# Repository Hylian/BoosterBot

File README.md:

BoosterBot
==========

A BoosterPack that turns your TI Launchpad into a fully functional robot!

The BoosterBot attaches underneath any 40-pin Launchpad to give it batteries, wheels, and access to a bunch of sensors; perfect for anyone who wants to get started with MSP430 and robotics, or just wants an easy to use robotics platform to build off of.

Features
--------
* Micro Metal Gearmotors from Pololu
* Powered by 3xAAA batteries
* Five QRE1113 Reflectance sensors for line following and maze solving
* Header for a Sharp IR distance sensor
* Header for a servo
* Compatible with other BoosterPacks, including the FuelTank battery BoosterPack

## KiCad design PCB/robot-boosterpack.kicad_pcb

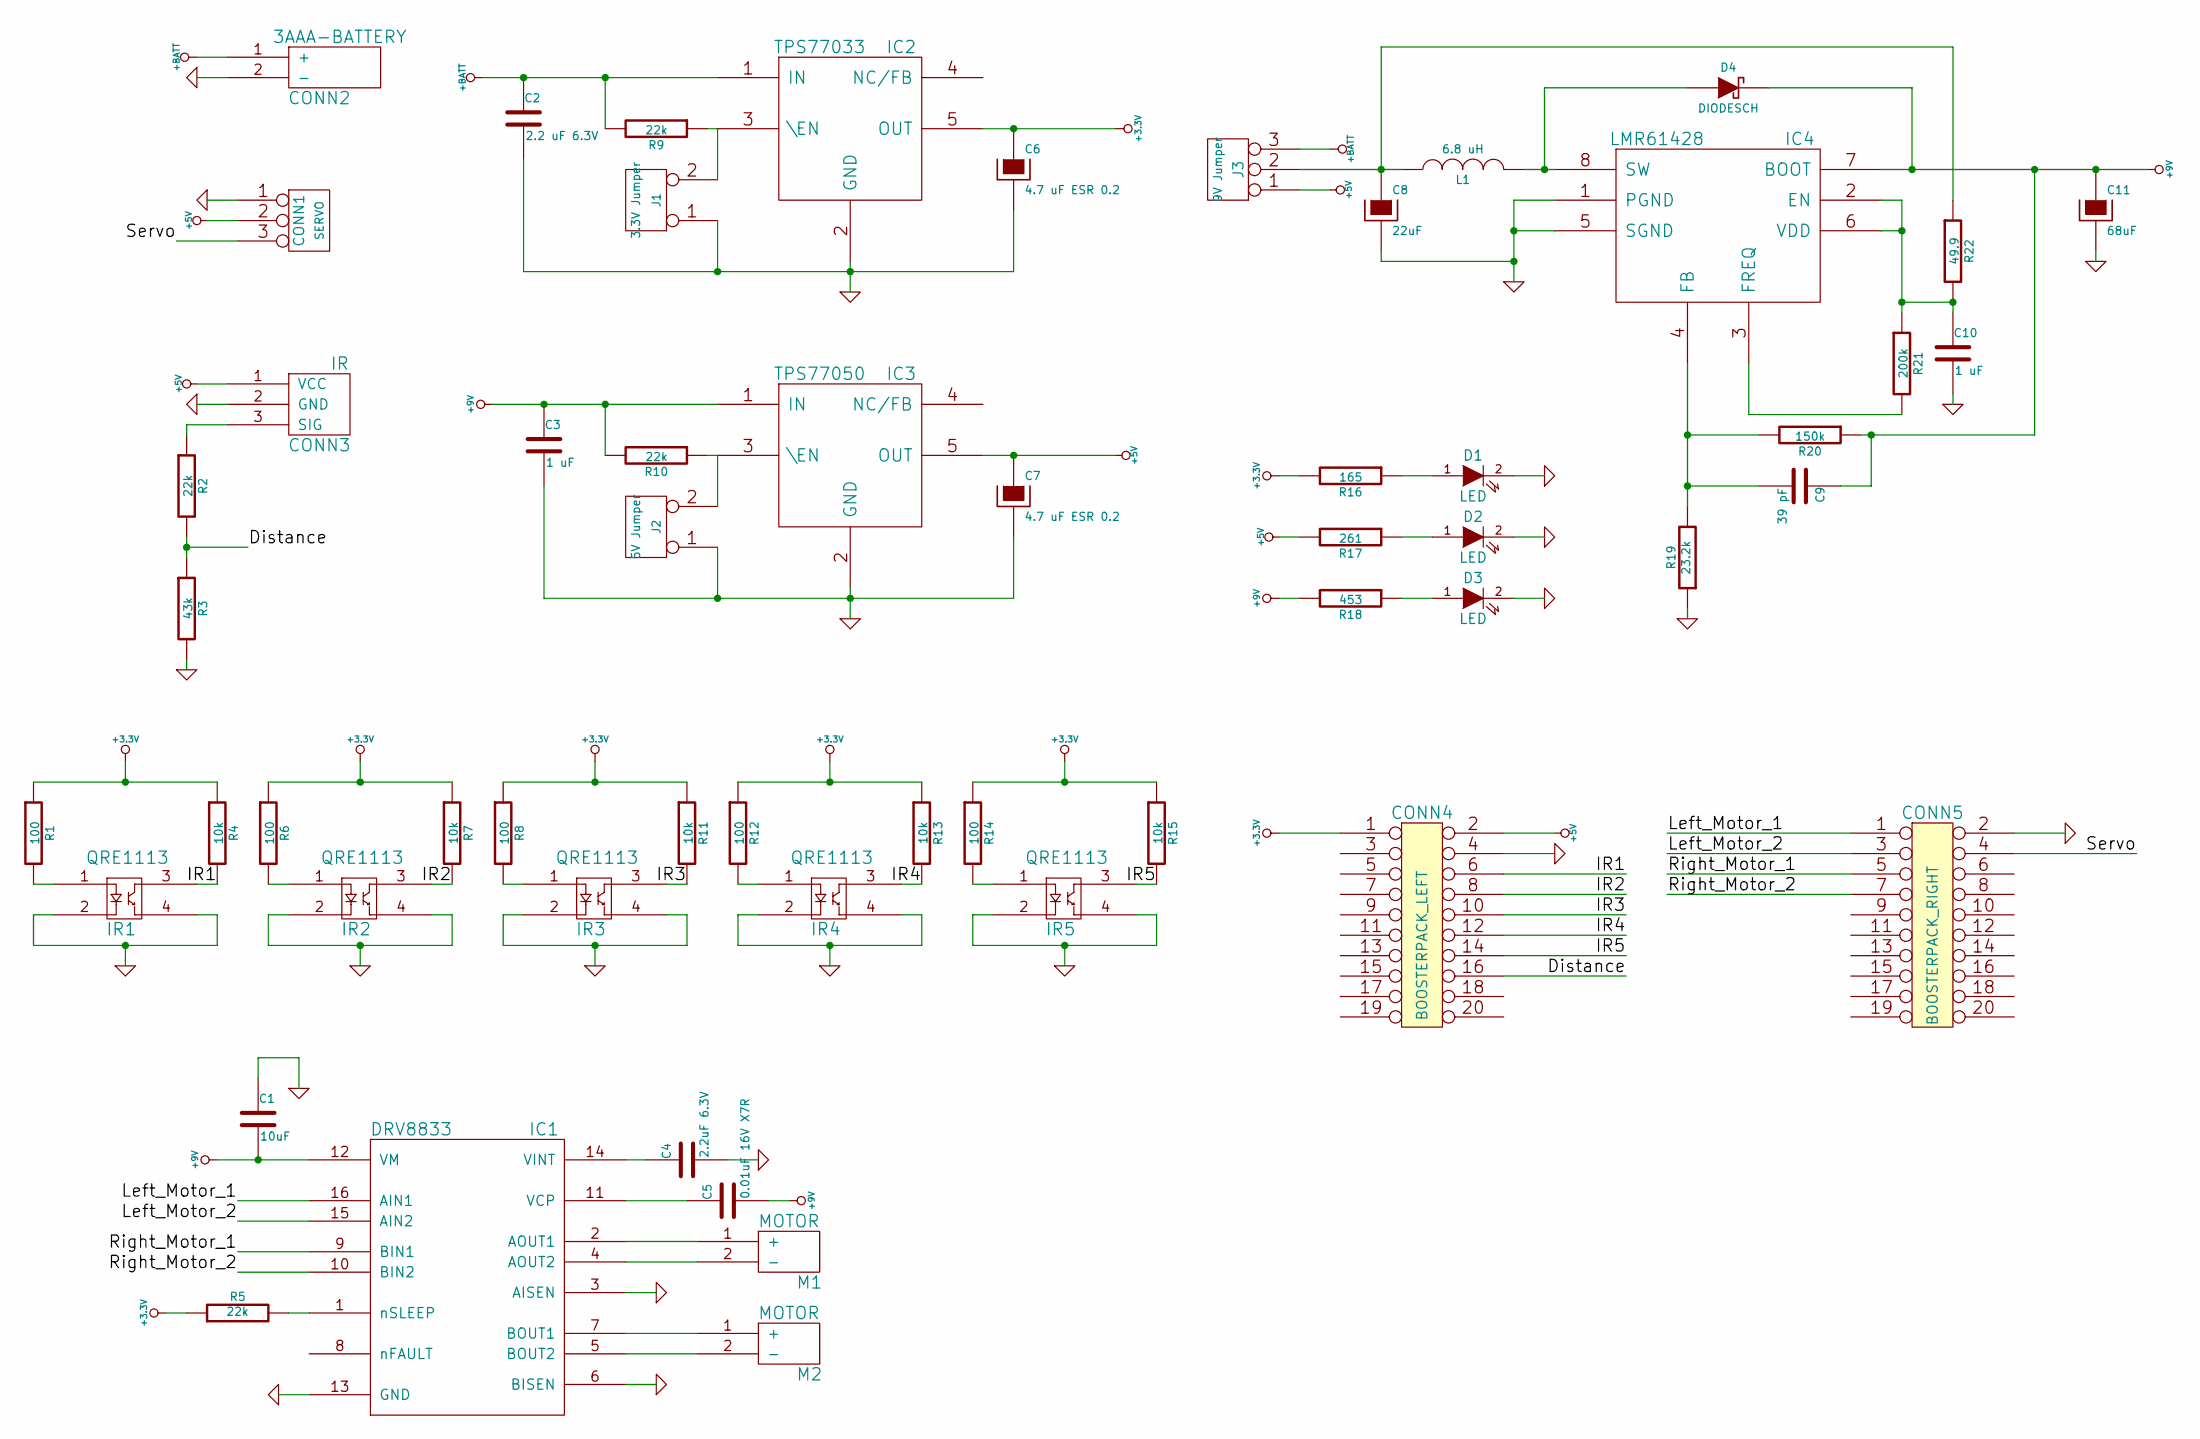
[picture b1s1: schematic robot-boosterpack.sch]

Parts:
C1: 10uF; Digikey # 311-1343-1-ND
C2: 2.2 uF 6.3V; Digikey # 587-1254-1-ND
C3, C10: 1 uF; Digikey # 587-1242-1-ND
C4: 2.2uF 6.3V; Digikey # 587-1254-1-ND
C5: 0.01uF 16V X7R; Digikey # 490-1512-1-ND
C6, C7: 4.7 uF ESR 0.2; Digikey # 478-1772-1-ND
C8: 22uF; Digikey # 399-3716-1-ND
C9: 39 pF
C11: 68uF; Digikey # 399-4698-1-ND
CONN1: SERVO; Digikey # 609-3461-ND
CONN2: 3AAA-BATTERY
CONN3: IR; Digikey # S5751-03-ND
CONN4: BOOSTERPACK_LEFT
CONN5: BOOSTERPACK_RIGHT
D1: LED; Digikey # 160-1448-1-ND
D2: LED; Digikey # 160-1447-1-ND
D3: LED; Digikey # 160-1647-1-ND
D4: DIODESCH; Digikey # MBRS140T3GOSCT-ND
IC1: DRV8833
IC2: TPS77033
IC3: TPS77050
IC4: LMR61428
IR1, IR2, IR3, IR4, IR5: QRE1113
J1: 3.3V Jumper; Digikey # 3M9447-ND
J2: 5V Jumper; Digikey # 3M9447-ND
J3: 9V Jumper; Digikey # 609-3461-ND
L1: 6.8 uH; Digikey # SRN6045-100MCT-ND
M1, M2: MOTOR
R1, R6, R8, R12, R14: 100; Digikey # 311-100HRCT-ND
R2, R5, R9, R10: 22k; Digikey # P22KDBTR-ND
R3: 43k; Digikey # 311-43.0KHRCT-ND
R4, R7, R11, R13, R15: 10k; Digikey # 311-10KGRCT-ND
R16: 165; Digikey # 311-165HRCT-ND
R17: 261; Digikey # P261HCT-ND
R18: 453; Digikey # P453HCT-ND
R19: 23.2k; Digikey # 311-23.2KHRTR-ND
R20: 150k; Digikey # P150KDBCT-ND
R21: 200k; Digikey # P200KDBCT-ND
R22: 49.9; Digikey # P49.9HCT-ND

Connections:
+3.3V: C6.1, CONN4.1, IC2.5 (OUT), R1.1, R4.1, R5.1, R6.1, R7.1, R8.1, R11.1, R12.1, R13.1, R14.1, R15.1, R16.2
+5V: C7.1, CONN1.2 (PM), CONN3.1 (VCC), CONN4.2, IC3.5 (OUT), J3.1, R17.2
+BATT: C2.1, CONN2.1 (+), IC2.1 (IN), J3.3, R9.2
/Distance: CONN4.16, R2.2, R3.1
/IR1: CONN4.6, IR1.3, R4.2
/IR2: CONN4.8, IR2.3, R7.2
/IR3: CONN4.10, IR3.3, R11.2
/IR4: CONN4.12, IR4.3, R13.2
/IR5: CONN4.14, IR5.3, R15.2
/Left_Motor_1: CONN5.1, IC1.16 (AIN1)
/Left_Motor_2: CONN5.3, IC1.15 (AIN2)
/Right_Motor_1: CONN5.5, IC1.9 (BIN1)
/Right_Motor_2: CONN5.7, IC1.10 (BIN2)
/Servo: CONN1.3, CONN5.4
GND: C1.1, C2.2, C3.2, C4.2, C6.2, C7.2, C8.2, C10.2, C11.2, CONN1.1, CONN2.2 (-), CONN3.2 (GND), CONN4.4, CONN5.2, D1.2 (K), D2.2 (K), D3.2 (K), IC1.3 (AISEN), IC1.6 (BISEN), IC1.13 (GND), IC2.2 (GND), IC3.2 (GND), IC4.1 (PGND), IC4.5 (SGND), IR1.2, IR1.4, IR2.2, IR2.4, IR3.2, IR3.4, IR4.2, IR4.4, IR5.2, IR5.4, J1.1, J2.1, R3.2, R19.1
unnamed: C9.2, IC4.4 (FB), R19.2, R20.2
unnamed: IC4.3 (FREQ), R21.2
unnamed: IR4.1, R12.2
unnamed: C10.1, IC4.2 (EN), IC4.6 (VDD), R21.1, R22.2
unnamed: IR3.1, R8.2
unnamed: IR2.1, R6.2
unnamed: C4.1, IC1.14 (VINT)
unnamed: C5.1, IC1.11 (VCP)
unnamed: IC1.1 (nSLEEP), R5.2
unnamed: IR1.1, R1.2
unnamed: CONN3.3 (SIG), R2.1
unnamed: D4.1 (A), IC4.8 (SW), L1.2
unnamed: D3.1 (A), R18.1
unnamed: D2.1 (A), R17.1
unnamed: D1.1 (A), R16.1
unnamed: C8.1, J3.2 (PM), L1.1, R22.1
unnamed: IC3.3 (\EN), J2.2 (PM), R10.1
unnamed: IR5.1, R14.2
unnamed: IC2.3 (\EN), J1.2 (PM), R9.1
unnamed: IC1.7 (BOUT1), M2.1 (+)
unnamed: IC1.5 (BOUT2), M2.2 (-)
unnamed: IC1.4 (AOUT2), M1.2 (-)
unnamed: IC1.2 (AOUT1), M1.1 (+)

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
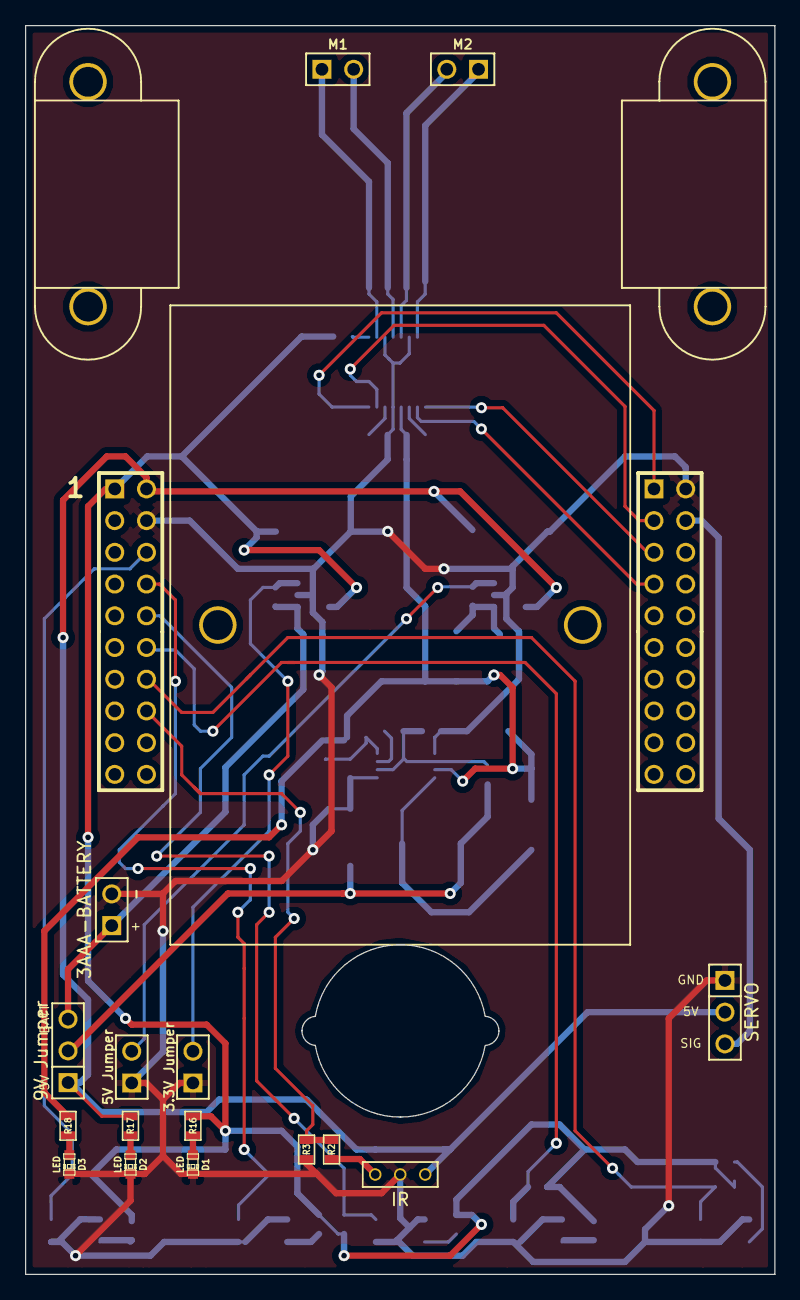
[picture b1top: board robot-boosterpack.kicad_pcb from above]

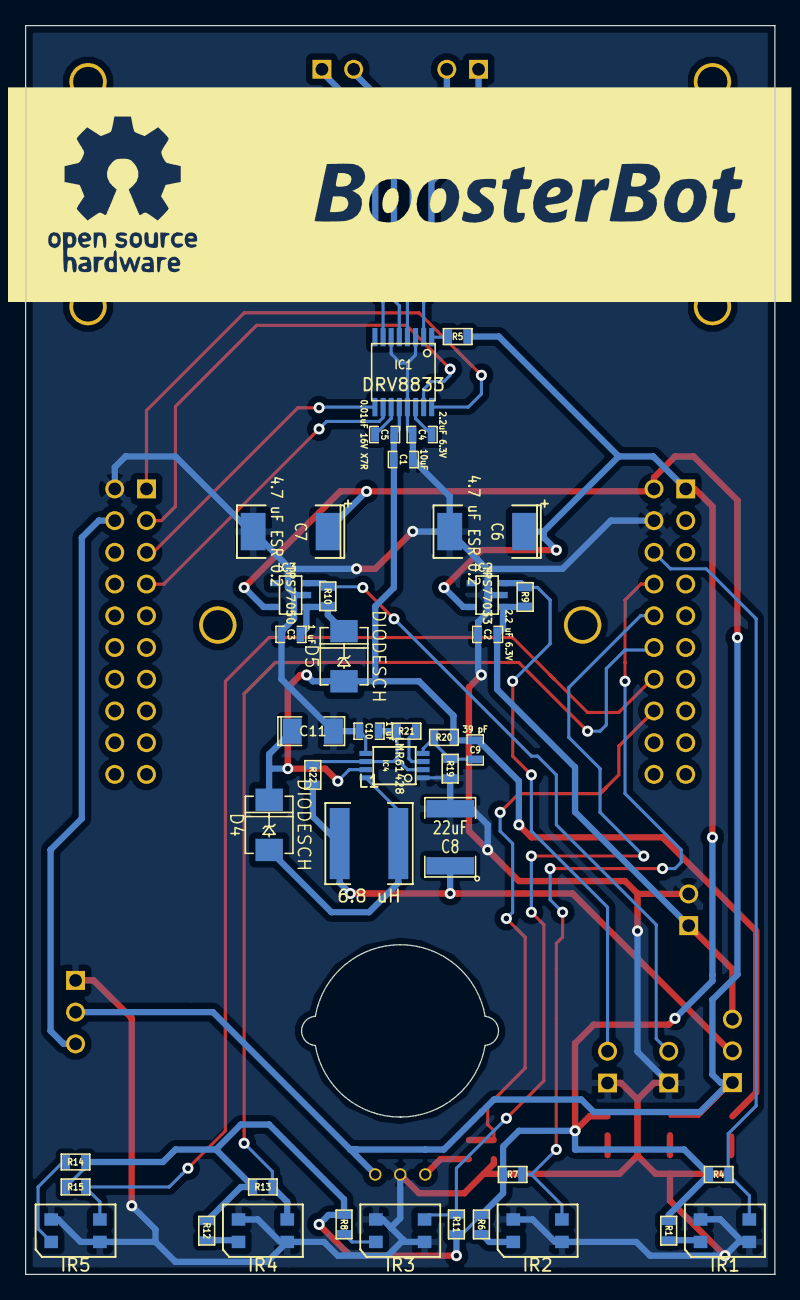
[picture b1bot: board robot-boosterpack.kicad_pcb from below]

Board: 2 copper layers, 60.0 x 100.0 mm, 61 parts (40 on the bottom side), 40 nets.

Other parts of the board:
BATTERY: P***; 3xAAA
D5: DIODESCH; DO-214AA(SMB)
GEARMOTOR: P***; 1pin
GEARMOTOR#2: P***; 1pin

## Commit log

2014-06-18 test commit
2014-06-18 Created KiCAD Schematic
2014-06-22 added libraries for motor driver, motor, and IR
2014-06-22 added reflectance sensor
2014-06-22 added battery holder
2014-06-23 fixed grid alignment on reflectance sensor
2014-06-23 created reflectance sensor circuit
2014-06-23 created motor controller circuit
2014-06-23 Misc changes
2014-06-23 added 3.3V regulator part
2014-06-23 created 3.3V regulator circuit
2014-06-23 created 12V regulator component
2014-06-23 created 10V regulator schematic
2014-06-24 added 5V regulator
2014-06-24 added 5V regulator circuit
2014-06-24 updated 5V regulator circuit
2014-06-24 updated 5V regulator capacitor values
2014-06-24 added servo connectors
2014-06-24 created boosterpack connections
2014-06-24 updated servo connector label
2014-06-24 added regulator jumpers
2014-06-25 annotated schematic
2014-06-25 changed output voltage of switching regulator to 9V from 10V
2014-06-25 changed switching regulator from bootstrap to non-bootstrapping mode
2014-06-25 re-annotated schematic
2014-06-25 replaced 10V labels with 9V labels
2014-06-25 added damping resistor to regulator circuit
2014-06-26 generated netlist
2014-06-27 added regulator status LEDs
2014-06-27 added gitignore
2014-06-27 generated netlist and BOM
2014-06-27 added part number for IR distance sensor connector
2014-06-27 added part numbers for LEDs
2014-06-27 updated netlist
2014-06-29 finished footprint association, added custom footprints
2014-06-29 created pcb file
2014-06-29 added pcb outline
2014-06-30 organized pcb components
2014-07-01 added motor mount drill holes
2014-07-02 made pcb edges align to 10mm grid
2014-07-02 centered LP headers
2014-07-02 fixed motor mount orientation
2014-07-02 modified reflectance sensor module and placement
2014-07-02 fixed resistor placement for reflectance sensors
2014-07-02 spaced out reflectance sensors and made room for distance sensor
2014-07-02 placed LP headers in their proper position
2014-07-02 reoriented LEDs so that they go beyond the LP pcb
2014-07-02 spaced out the LEDs some more for silkscreen room
2014-07-02 lengthened board to make room for distance sensor
2014-07-02 added motor outline
2014-07-02 added battery drill module
2014-07-02 moved motor driver around to fit battery
2014-07-02 reoriented motor driver
2014-07-03 replaced inductor with smaller part
2014-07-03 added pololu 3/8" caster
2014-07-03 polished up silk
2014-07-03 added inductor silk
2014-07-03 moved motor connectors so silk is visible
2014-07-03 brought invisible pololu labels inside drill
2014-07-03 ir silk label
2014-07-03 fixed up more silk
2014-07-03 misc silk
2014-07-05 moved battery connector
2014-07-07 initial bad routing
2014-07-07 finished basic routing, expanded trace width
2014-07-07 fixed IR sensor being backwards
2014-07-07 added ground planes
2014-07-08 logo and gerbers to send to fab
2014-07-09 updated README with new name
2014-07-11 initial motor driver library
2014-07-11 removed extra motor library files
2014-07-27 Fixes to motor lib
2014-07-28 Fixed motor library
2014-07-28 Added PID library
2014-07-28 Basic line tracking demo
2014-07-30 working distance tracking demo
2014-07-30 basic functional line tracking code
2014-07-30 distance tracking libs
2014-07-30 tuned PID
2014-07-30 working basic distance sensor transmit/receive using AIR
2014-07-30 consolidated AIR demo into one folder
2014-07-31 pre-video commit
2014-08-19 Rev 1.1
2014-08-21 Fixes for unupdated ground plane!
2015-06-12 added Tindie link
2016-06-09 add pdf file
